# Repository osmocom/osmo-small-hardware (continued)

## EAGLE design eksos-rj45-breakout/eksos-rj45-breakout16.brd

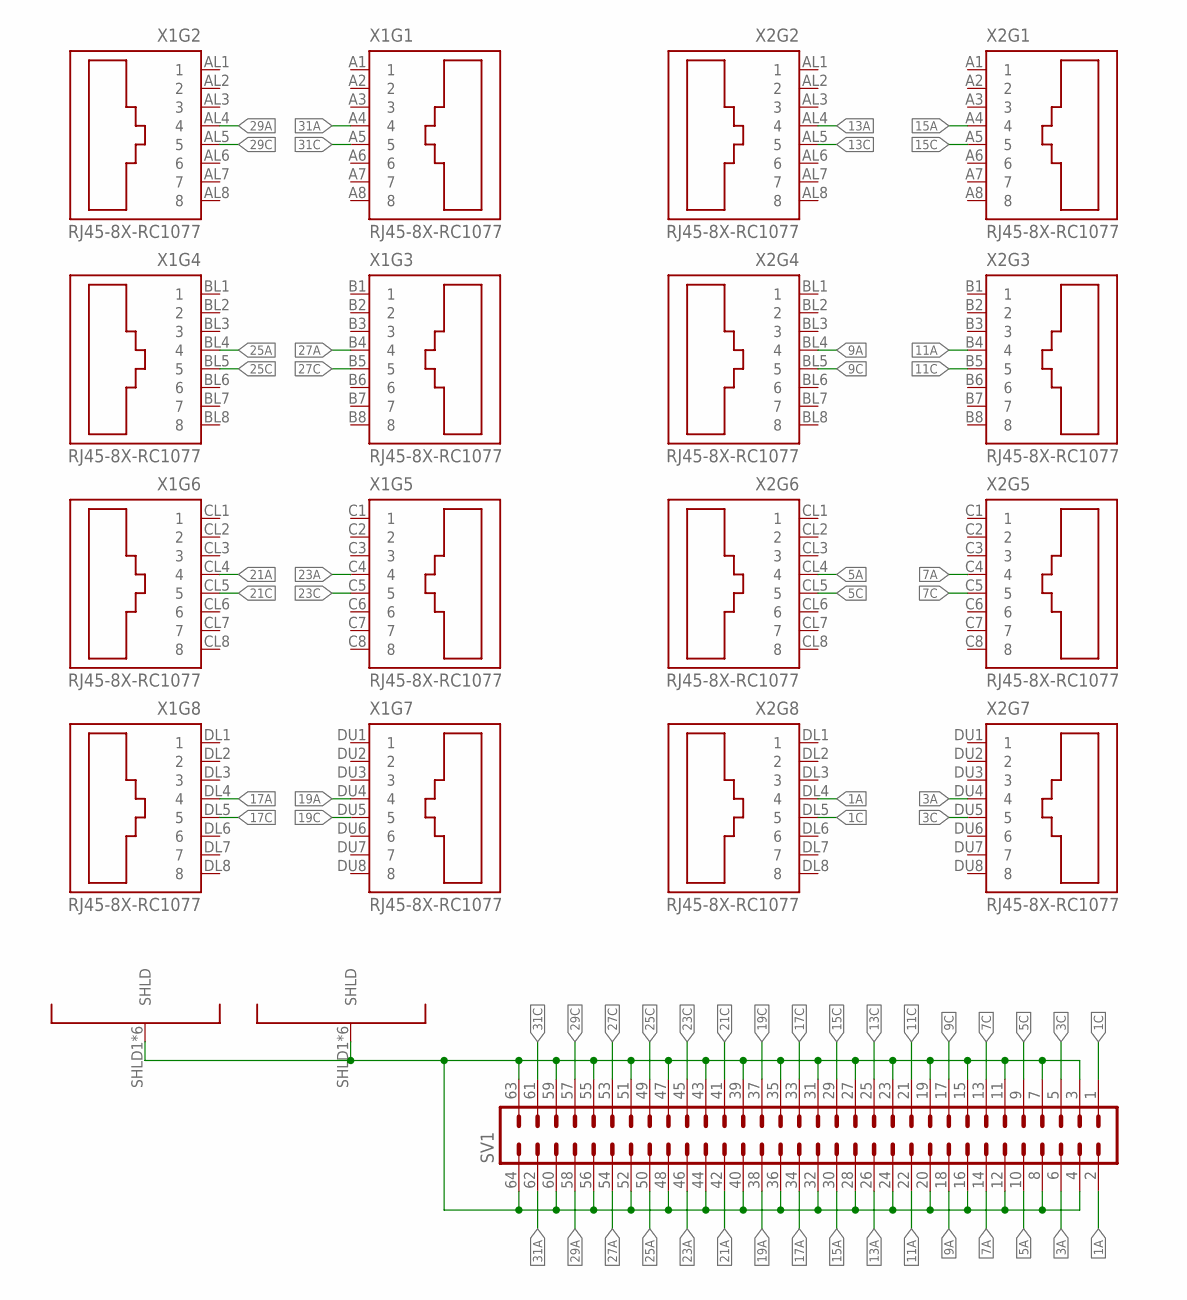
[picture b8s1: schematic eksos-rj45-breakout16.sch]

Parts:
SV1: ML64
X1, X2: RJ45-8X-RC1077; RC01077

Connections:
1A: SV1.2, X2.DL4 (4)
1C: SV1.1, X2.DL5 (5)
3A: SV1.6, X2.DU4 (4)
3C: SV1.5, X2.DU5 (5)
5A: SV1.10, X2.CL4 (4)
5C: SV1.9, X2.CL5 (5)
7A: SV1.14, X2.C4 (4)
7C: SV1.13, X2.C5 (5)
9A: SV1.18, X2.BL4 (4)
9C: SV1.17, X2.BL5 (5)
11A: SV1.22, X2.B4 (4)
11C: SV1.21, X2.B5 (5)
13A: SV1.26, X2.AL4 (4)
13C: SV1.25, X2.AL5 (5)
15A: SV1.30, X2.A4 (4)
15C: SV1.29, X2.A5 (5)
17A: SV1.34, X1.DL4 (4)
17C: SV1.33, X1.DL5 (5)
19A: SV1.38, X1.DU4 (4)
19C: SV1.37, X1.DU5 (5)
21A: SV1.42, X1.CL4 (4)
21C: SV1.41, X1.CL5 (5)
23A: SV1.46, X1.C4 (4)
23C: SV1.45, X1.C5 (5)
25A: SV1.50, X1.BL4 (4)
25C: SV1.49, X1.BL5 (5)
27A: SV1.54, X1.B4 (4)
27C: SV1.53, X1.B5 (5)
29A: SV1.58, X1.AL4 (4)
29C: SV1.57, X1.AL5 (5)
31A: SV1.62, X1.A4 (4)
31C: SV1.61, X1.A5 (5)
SHLD: SV1.3, SV1.4, SV1.7, SV1.8, SV1.11, SV1.12, SV1.15, SV1.16, SV1.19, SV1.20, SV1.23, SV1.24, SV1.27, SV1.28, SV1.31, SV1.32, SV1.35, SV1.36, SV1.39, SV1.40, SV1.43, SV1.44, SV1.47, SV1.48, SV1.51, SV1.52, SV1.55, SV1.56, SV1.59, SV1.60, SV1.63, SV1.64, X1.SHLD1 (SHLD), X1.SHLD2 (SHLD), X1.SHLD3 (SHLD), X1.SHLD4 (SHLD), X1.SHLD5 (SHLD), X1.SHLD6 (SHLD), X2.SHLD1 (SHLD), X2.SHLD2 (SHLD), X2.SHLD3 (SHLD), X2.SHLD4 (SHLD), X2.SHLD5 (SHLD), X2.SHLD6 (SHLD)

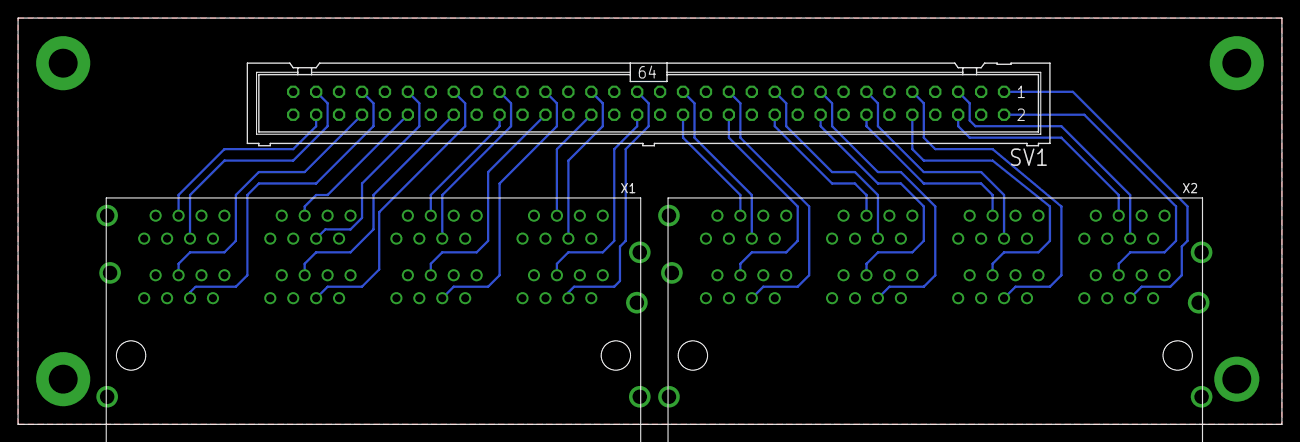
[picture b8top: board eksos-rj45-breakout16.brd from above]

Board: 2 copper layers, 140.0 x 45.0 mm, 3 parts (0 on the bottom side), 33 nets.

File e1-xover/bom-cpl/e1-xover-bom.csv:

Comment,Designator,Footprint,JLCPCB Part #
LED1,LED1,MHK2512RGTD,C473819
Resistors,"R1,R2",0207/7,C120007
Pushbutton,PB1,SH-5.8ZSPT,C2681588
Switch,SW1,K3-2268T,C502351
RJ45,"X1,X2",HC-RJ45-5JA-1-6,C3000176

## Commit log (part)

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2016-10-07 WIP: design for a multi-voltage USB UART
    * an adjustible LDO with rotary switch is able to configure the UART
    voltage levels as needed.
    * alternatively, the UART logic level voltage (in the 1.8-3.3V range)
    can be provided by an external voltage reference.
    * TVS diodes protect the USB and UART sides from overvoltage and ESD
    * all voltages are available on a header to supply external circuitry
2016-10-08 move all mv-uart files to sub-directory
2016-10-08 mpcie-breakout: add rendered gerber files
2016-10-08 mv-uart: use Seeed Studio DRU
2016-10-09 mv-uart: Add digikey link for all major parts
2016-10-09 mv-uart: Add PDF renderings
2016-10-10 add .gitignore
2016-10-27 mv-uart: Use SP6T flash *without* OFF position
2016-10-27 mpcie-breakout: Add series LED for LED_WWAN
2016-10-28 add PCB panel images for mv-uart and mpcie-breakout
2016-10-28 mv-uart: Add schematics + placement as PDF
2016-10-28 mpcie-breakoud: Add pdf renderings of schematics
2017-03-23 mpcie-breakout: Enlarge to 70x70mm, add SMA, U.FL and Mounting Holes
2017-03-23 mcie-breakout: Align bLabels, more vias, cosmetics
2017-03-23 mpcie-breakout: disable tPlace layer
2017-03-23 mpcie-breakout: Change to vertical SMA jacks
2017-03-23 mpcie-breakout: update BOM
2017-03-27 Add ngff-breakout as copy of mpcie-breakout
    ... ngff specific modifications will follow
2017-04-04 mpcie-breakout: update .mnt/.mnb files with v3 pcb
2017-05-07 import e1-tap design files
    This is a project started in 2012 to have an easy-to-use E1/T1 tap.
2017-07-22 mv-uart: annotate individual pins in brd and generate mv-uart-pinout.pdf
2018-06-07 sfp: add Eagle lib for SN65LVDS180 LVDS diff line xcvr
2018-06-19 sfp: add license to sch
2018-08-17 spf: revise both SFP designs (OSM#3313/OSM#3314)
2018-08-21 sfp: Use minimum clearance of 0.25mm as 0.15mm is needlessly tight in this board
2018-08-30 sfp: add part numbers for SFP conn and cage
2018-10-06 add SFP multi-source agreement to give context to the boards
2019-01-21 clock-generator: More work on schematics (USB, UART, ESD)
2019-01-26 clock-gen: Add SPI; UEXT header; mounting holes; do layout/routing
2019-01-27 clock-gen: finish routing of PCB layout
2019-01-27 clock-gen: Update gpio spreadsheet with all assignments
    The assignments have been chosen to be nearly identical to the
    SAMD11-XPRO board.
2019-02-14 clock-converter: Add attributes with digikey links
2019-05-08 sfp: update BOMs for both breakout and experimenter PCBs
2019-06-12 ngff-breakout: make 4layer PCB
2019-06-19 clock-generator: add tracking LDO, make PCB four layer
2019-06-19 clock-generator: compacting + place MTA100 header (solves OSM#4050)
2019-06-19 clock-generator: changes adressing OSM#4050
    A shouded UEXT would need much space; no room for an MTA100 yet... tbd
2019-06-22 add placement files for top and bottom
2019-06-22 add CAM file for generating gerber output
2019-06-22 update gerbers...
2019-06-22 add fiducials for automatic mounting of components
2019-06-22 component placement PDFs bottom and top
2019-06-22 don't put solder cream on SMA edge pads.
    The sma edge connectors are hand soldered after the SMT soldering
    is already done. We don't want to have solder paste on them...
2019-06-22 add updated PDF schematics
2019-06-22 initial import of osmo-nvs-gps project
    This is a small eval board for the NVS GPS/GLONASS/GALILEO module,
    exporting UARTs on headers.
2019-06-22 add gerber output of osm-nvs-gps v3
2019-06-22 final v3 as it goes in pcb production
    * smash components and move labels to where they can be read
    * add indication of + / GND to X3/X4
    * re-route some traces to ensure sufficient distance between them
    * make all traces 0.508 mm wide, even signal traces.
2019-06-22 v3 final with gerber output
2019-08-07 add SC14CVMDECT module breakout board
2019-08-27 ngff: finishing work
2019-09-17 ngff: set R9 to 100k (solves OS#4209)
2019-09-19 ngff: remove bogus packages names with '@1' by re-importing std lib
2019-09-24 ngff: repair one critical via for ERC passing
2019-09-25 ngff: add / refresh most ext'd attribs for eBOM
2019-10-17 ngff: connect pin 4 @X2 to GND (solves OS#4216)
2019-10-18 ngff: revert increased clearance for supply net class
    ...and instead change class membership of an affected wire.
2019-11-22 ngff-breakout: update BOM
2020-01-09 ngff: add product links to all one- and two-row 2,54mm pin header
2020-01-31 clock-gen: update ATSAMD21's BOM attributes (solves OS#4387)
2020-04-20 initial commit for a GTM900 breakout PCBA
    An additional mirrored FPC header will still be maintained
    as long as this PCBA is discussed/revised.
    This is going to be a OSHW CC-BY-SA.
2020-05-18 gtm900-bo: routing done, no airwires left, mirrored FPC removed
2020-05-19 gtm900-bo: re-introduce serial 0R on UART_RI
    ...not, that it was needed, but just in case...
2020-05-27 gtm900-bo: complete v1 eBOM + export as gnumeric and xls format
2020-06-04 gtm900-bo: exchange main LDO's BOM attributes
    Although the correct name was given in the schematic (MCP1827T-ADJE/ET),
    the BOM contained an LD1085, which is part of the same library...
    Now the extended attributes also reflect the correct part.
2020-06-08 clock-generator: update schematics pdf
2020-07-07 clock-generator: upd ext'd BOM attributes and update v2 eBOM
2020-07-17 add SIU clock breakout board design
    This board contains a 10P10C connector in the same pin-out as the
    Ericsson SIU-02 together with some differential receivers/drivers to
    convert the 1PPS from/to single-ended signals.
2020-07-27 siu-clock-breakout: Add missing component values
2020-09-10 mpcie-breakout: Remove GND via underneath U.FL connectors
2020-10-09 siu-clock-breakout: Add actual fischer TFP 4 outline
2020-10-09 clock-generator-frontpanel: Fix spacing of panel mount cut-outs
    they must not be symmetric, but in multiple of 5.08mm
2020-10-14 add export DXF for production (mirrored)
2020-11-01 initial design for DUS LMT breakout board
2021-01-11 ngff-breakout: add BOM attributes for 2.45mm stand-off and M.2 conn
2021-01-29 ngff-breakout: improve GND around 4th MHF4-SMA section
2021-03-21 add README.md on what this repository is all about
2021-03-30 README.md fix urls for cloning and cgit
2021-04-23 ngff-cardem: start design
2021-04-24 ngff-cardem: better function groups' placement
2021-04-26 ngff-cardem: remove SIM switch trio and connect straight to pivot
    This way the close-pivot OE is the only which needs a pull-down.
    Seven FET switches remain for other uses, four of them in a now
    usused seperate OE group.
2021-05-19 ngff-cardem: state w/ changes as of 18th May
2021-06-03 ngff-cardem: reduce number of options jumper to 3
2021-06-04 ngff-cardem: add SIM Vcc switch logic
    ... consisting of two FPF2109 and a Schottky diode. Needs two GPIOs,
    PU and PD for default "modem gives SIM pwr".
2021-06-04 ngff-cardem: bring /FLAG of IC1 to a GPIO (solves SYS#5477)
    GPIO is PA8 (former QMOD's 'SIMPRES2').
    Note, that the OCP of the FPF2109 is 200mA; there is no 100mA version
    in this series and w/ 1V8 lowest Vin.
2021-06-06 ngff-cardem: 4-position jumper conn instead 3 pos. w/ NGFF_RESET exposed
    ... on an OC inverter
2021-06-09 ngff-cardem: connect both SIMTRACE LEDs and assign to GPIOs
    ... like in the QuadModem for the first slot, the secont one like
    in the Simtrace
    adresses: SYS#5472
2021-06-10 ngff-cardem: update from 'rc-sysmocom.lbr' to purge footprints w/ "..@1"
2021-06-11 ngff-cardem: length matching for USB3
2021-06-13 ngff-cardem: add proper floppy power conn w/ a 2-resistor solder switch
2021-06-13 ngff-cardem: examine ERC + DRC for new part
2021-06-13 ngff-cardem: run renumber-sheet.uld and normalize-texts2.ulp
2021-07-05 add ncn8025-brekaout board
    This is a small eval/breakout board for the NCN8025 smart card interface IC
2021-09-03 sfp-experimnter: update extd attribs on D1, D2 to avail types
2021-09-08 ngff-cardem: populate R102 to uncond' release /NGFF_RESET (solves SYS#5531)
2021-09-09 ngff-cardem: split C301 into two footprints (solves SYS#5614)
2021-09-09 ngff-cardem: adjust setting resistors for Murata OKL (solves SYS#5613)
2021-09-22 ngff-cardem: improve clearance details to gain lower tech class than 8
    ... at Eurocircuits
2021-09-24 ngff-cardem: correct typo and add silk screen in bott name plate
2021-12-23 Add bgt-pwr-dist; A 3U component-carrier DC distribution module
2021-12-23 Add component carrier module mechanics for Ettus USRP B2xx
2022-01-31 bgt-pwr-dist: Finalize v2
    * no milling for DC jack (cheaper PCB production)
    * update version to v2
2022-02-14 bgt-pwr-dist: Increase restring on bottom side
    (v2 only increased it on top side, my mistake)
    Incremental fix for 84166fd4abd70575491d5e001d1fde690e2611e7
2022-03-24 ngff-cardem: Add PDF renderings of schematics + component placement
2022-05-13 xhfc-breakout: Data sheets of transformer and BAV99 diode
2022-05-13 xhfc-breakout: Complete line interface from chip to RJ45
2022-05-13 xhfc-breakout: bom attributes
2022-06-04 xhfc-breaout: Conncet SPI_INV to GND
    This was missing from the v1 design. SPI_INV must be tied to either high
    or low to select the SPI clock polarity. It was tied to low by manawyrm
    in his manual rework, so let's reflect this in the design accordingly.
2022-09-19 ngff-cardem: connect OsmoSer's GND to GND (solves SYS#5514)
    This change somehow didn't make it upstream though committed as
    bf211d3; so recreated.
2022-10-22 initial check-in of bgt-keystone project
    This adds a 3U component carrier module into which you can mix and
    match keystone modules as needed.
2023-01-20 rj45_jumper_box: Use different RJ45 jack; both on top layer
    The original design (one RJ45 on top, one on bottom) was easy to route
    but was difficult to handle. Let's swap both connectors to top, and use
    a low-cost Chinese RJ45.
2023-02-03 initial version of bgt-gs305e: BGT Mount for Netgear GS305E switch
2023-02-12 New design: plutosdr-revb-extclk
    This is a small circuit board containing the "external clock ref input"
    circuitry that was added to PlutoSDR RevD. It can be used to
    upgrade/rework RevB boards with the same clock input as the later RevD.
    Related: OS#5892
2023-04-14 sfp-*: change all 10µF/16V 0805 to 1206 (solves SYS#5397)
    also update all URLs to the current Digikey URI scheme
2023-05-15 sfp-experimenter: insert main fiducials
2023-07-02 plutosdr-revb-extclk: don't shut-down LTC via SD1/SD2
    In the original PlutoSDR RevC or higher, there's a BSS138 FET
    that [optionally] pulls low the SD1/SD2 pins in order to activate
    the external clock input.
    In this circuit, we don't have GPIO control but permanently enable
    the LTC.
    Related: OS#5892
2023-08-11 RJ45 breakout board for NOKA EKSOS ISDN / POTS ports
    These board designs assumes that you use a 64pos (type 3 a+c)
    DIN-connector with a flat ribbon cable to a 2x32 2.54mm pitch (IDE/SCSI
    style) header to interconnect them.
    The point is that assembling that ribbon cable with IDC technology is
    much faster than performing soldering or LSA+ type termination on 32
    individual wires.
2023-08-11 eksos-rj45-breakout16: ad label/copyright/license/OSHW
2023-08-11 README.md: Add note about EKSOS breakout boards
2023-08-21 amr-breakout: Add pull-ups for !AC97_RESET and !PRIMARY_DN
    Closes: OS#5369
2023-10-10 gtm900-breakout: add next design v3
2023-11-02 gtm900-bo: rename main files w/o explicit version
2023-11-06 gtm900-bo: add 47R into both UARTs' wires
2023-11-15 gtm900-bo: update v3 schema pdf
2024-01-18 gtm900-bo: change silkscreen name to 'OsmoGTM900 breakout v3'
2024-02-27 gtm900-bo: new SIM holder, add LCSC part numbers
    Now using a XunPu SIM-105B-ARP8 SIM holder which is somewhat close
    to the JAE SF7W008S1A.
2024-03-21 gtm900-bo: replace JLCPCB cpl file
    The missing T1,T2 now are in.
2024-05-08 ngff-cardem: update schema pdf
2024-10-26 rbs6k-dyi-rack: add rbs6k diy rack top/bottom panel drawing
2024-10-26 rbs6k-diy-rack: Add CC-BY-SA COPYING file
2024-10-26 rbs6k-dyi-rack: rbs6k_fan-hood_*.dxf - add centerlines to help layer, add marking layer for drillholes (only markings, no holes)
2024-10-26 rbs6k-dyi-rack: add first sketch for a hood to add fans to the 8U rbs6k frames
    no rounded corners yet
2024-10-26 rbs6k-dyi-rack: diy-rack: MeanWell RSP-750 power supply drawing
2024-11-17 GTM900: Add missing bottom solder mask layer
2024-12-04 Add a small break-out board for the FCD-155 8xE1 DB44 connector
2025-01-02 fcd-155-breakout: Fix pin-out for even numbered ports
    Related: OS#6678
